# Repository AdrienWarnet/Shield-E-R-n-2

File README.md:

# Shield-E-R-n-2
Réalisation d'un Shield arduino
Programes ainsi que fichier Kikad de la carte

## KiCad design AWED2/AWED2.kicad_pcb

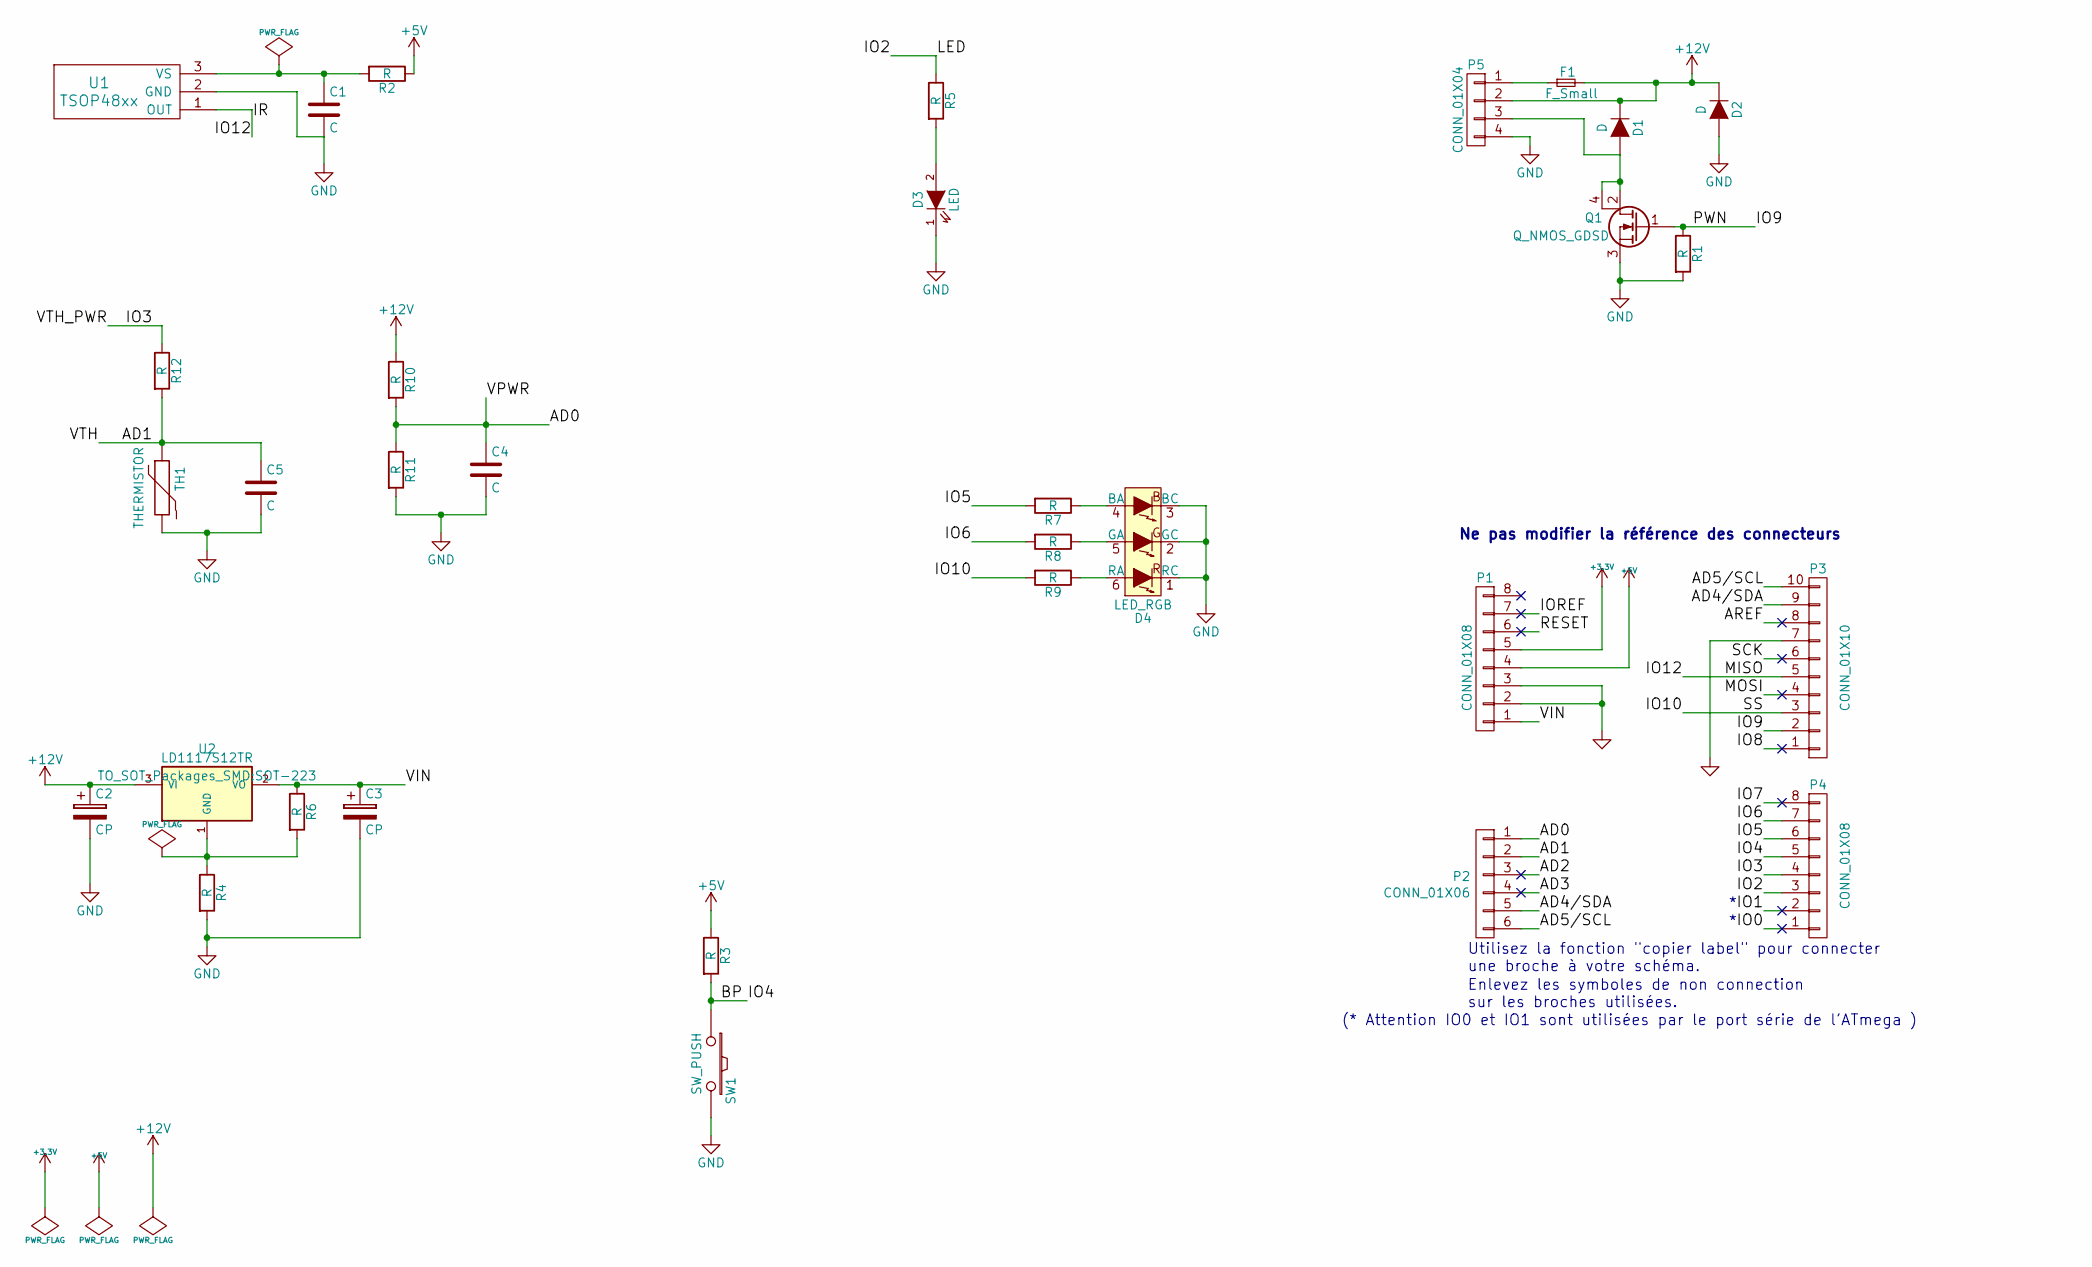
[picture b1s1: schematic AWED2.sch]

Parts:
C1, C4, C5: C; C_0805
C2, C3: CP; c_elec_4x4.5
D1, D2: D; SOD-123
D3: LED; LED_0805
D4: LED_RGB; LED_RGB_PLLC-6
F1: F_Small; SMD-1210_Pol
P1, P4: CONN_01X08; IUT-SIL-8
P2: CONN_01X06; IUT-SIL-6
P3: CONN_01X10; IUT-SIL-10
P5: CONN_01X04; IUT-bornier4
Q1: Q_NMOS_GDSD; D-Pak_TO252AA
R1, R2, R3, R4, R5, R6, R7, R8, R9, R10, R11, R12: R; R_0805
SW1: SW_PUSH; IUT-PUSH_SW-6x6-5x10-SMD
TH1: THERMISTOR; IUT-bornier2
U1: TSOP48xx; IUT-SIL-3
U2: LD1117S12TR; SOT-223

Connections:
+3V3: P1.5
+5V: P1.4, R2.1, R3.1
+12V: C2.1, D1.1 (K), D2.1 (K), F1.2, P5.2, R10.1, U2.3 (VI)
/AD0: C4.1, P2.1, R10.2, R11.1
/AD1: C5.1, P2.2, R12.2, TH1.1
/AD2: P2.3
/AD3: P2.4
/AD4/SDA: P2.5, P3.9
/AD5/SCL: P2.6, P3.10
/AREF: P3.8
/BP: P4.5, R3.2, SW1.1
/IO0: P4.1
/IO1: P4.2
/IO2: P4.3, R5.1
/IO3: P4.4, R12.1
/IO5: P4.6, R7.2
/IO6: P4.7, R8.2
/IO7: P4.8
/IO8: P3.1
/IO9: P3.2, Q1.1 (G), R1.1
/IO10: P3.3, R9.2
/IO12: P3.5, U1.1 (OUT)
/IOREF: P1.7
/MOSI: P3.4
/RESET: P1.6
/SCK: P3.6
/VIN: C3.1, P1.1, R6.1, U2.2 (VO)
GND: C1.2, C2.2, C3.2, C4.2, C5.2, D2.2 (A), D3.1 (K), D4.1 (RC), D4.2 (GC), D4.3 (BC), P1.2, P1.3, P3.7, P5.4, Q1.3 (S), R1.2, R4.2, R11.2, SW1.2, TH1.2, U1.2 (GND)
unnamed: C1.1, R2.2, U1.3 (VS)
unnamed: D1.2 (A), P5.3, Q1.2 (D), Q1.4 (D)
unnamed: D3.2 (A), R5.2
unnamed: D4.4 (BA), R7.1
unnamed: D4.5 (GA), R8.1
unnamed: D4.6 (RA), R9.1
unnamed: F1.1, P5.1
unnamed: R4.1, R6.2, U2.1 (GND)

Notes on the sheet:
Enlevez les symboles de non connection sur les broches utilisées.
Utilisez la fonction "copier label" pour connecter une broche à votre schéma.
Ne pas modifier la référence des connecteurs
(* Attention IO0 et IO1 sont utilisées par le port série de l'ATmega )

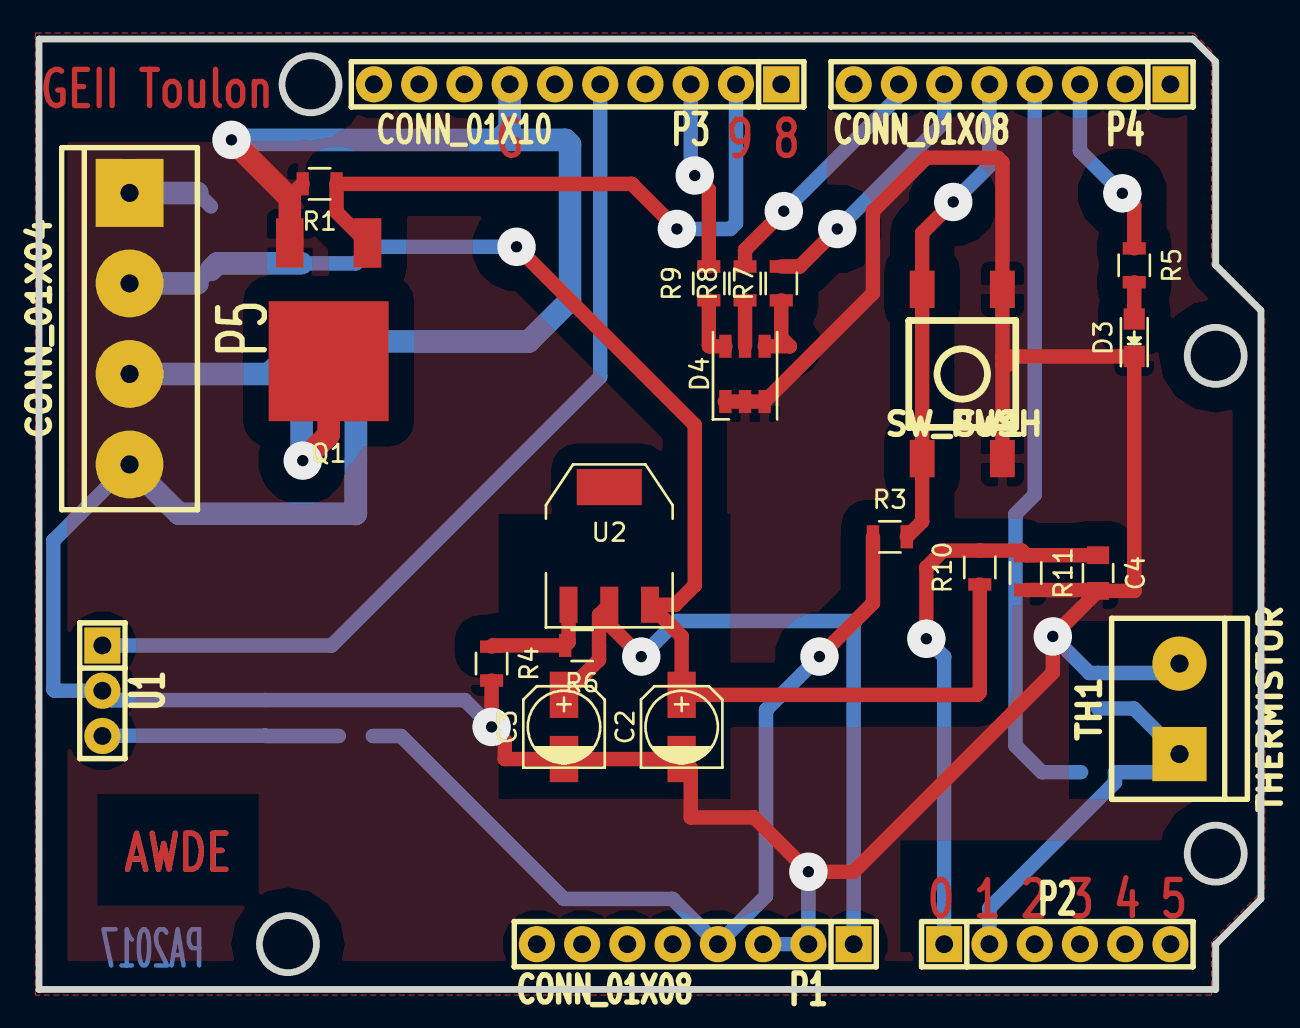
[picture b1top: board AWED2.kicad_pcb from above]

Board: 2 copper layers, 68.6 x 53.3 mm, 32 parts (0 on the bottom side), 24 nets.
